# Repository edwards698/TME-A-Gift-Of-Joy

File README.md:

# Tech Master Event-The Gift Of Joy Christmas Project

The Gift of Joy is a festive project designed to bring the spirit of Christmas to life through a combination of 
electronics and creativity. This open-source project incorporates an Arduino Nano with an ATmega328 microcontroller, 
an LCD display (16x2), 5 LEDs, 5 100-ohm resistors, a 10K potentiometer, a push button, and a buzzer. Spreading the joy and celebrate the Christmas season by coming up with your own Gift of Joy open Source. 

Lets celebrate this festive season together 

### Tech Master Event

https://techmasterevent.com/

The Gift of Joy" is published as an open-source project, inviting others to learn from, modify, and contribute to the code and hardware design. By sharing the joy of Christmas through this project, the hope is to inspire others to build their own festive creations and share them with the community.

### Dependencies
```C++
#include <LiquidCrystal.h>
```

```C++
const int rs = 12, en = 11, d4 = 5, d5 = 4, d6 = 3, d7 = 2;
LiquidCrystal lcd(rs, en, d4, d5, d6, d7);
```

### Schematic 

## Components 
### Arduino Nano (ATmega328):
The brain of the project, responsible for controlling and coordinating all the connected components.

### LCD Display (16x2): 
This display serves as the interface, providing visual feedback and information about the project.

### 5 LEDs with 100-ohm resistors: 
These LEDs are used to create a colorful light display, representing the joy and festivity of Christmas.

### 10K Potentiometer: 
The potentiometer can be used to adjust settings or parameters, adding an element of user interaction to the project.

### Push Button:
A push button allows users to trigger specific actions or functions, enhancing the interactivity of the project.

### LED Display: 
The 5 LEDs can be programmed to light up in different patterns or sequences, creating visually appealing light displays.

### Interactive Features:
Program the push button to trigger the buzzer to play Christmas melodies.

### Adjustable Settings:
Utilize the potentiometer to allow users to adjust settings

### Buzzer Melodies: 
Program the buzzer to play festive tunes or sound effects, enhancing the overall Christmas experience.

"The Gift of Joy" is published as an open-source project, inviting others to learn from, modify, and contribute to the code and hardware design. By sharing the joy of Christmas through this project, the hope is to inspire others to build their own festive creations and share them with the community.

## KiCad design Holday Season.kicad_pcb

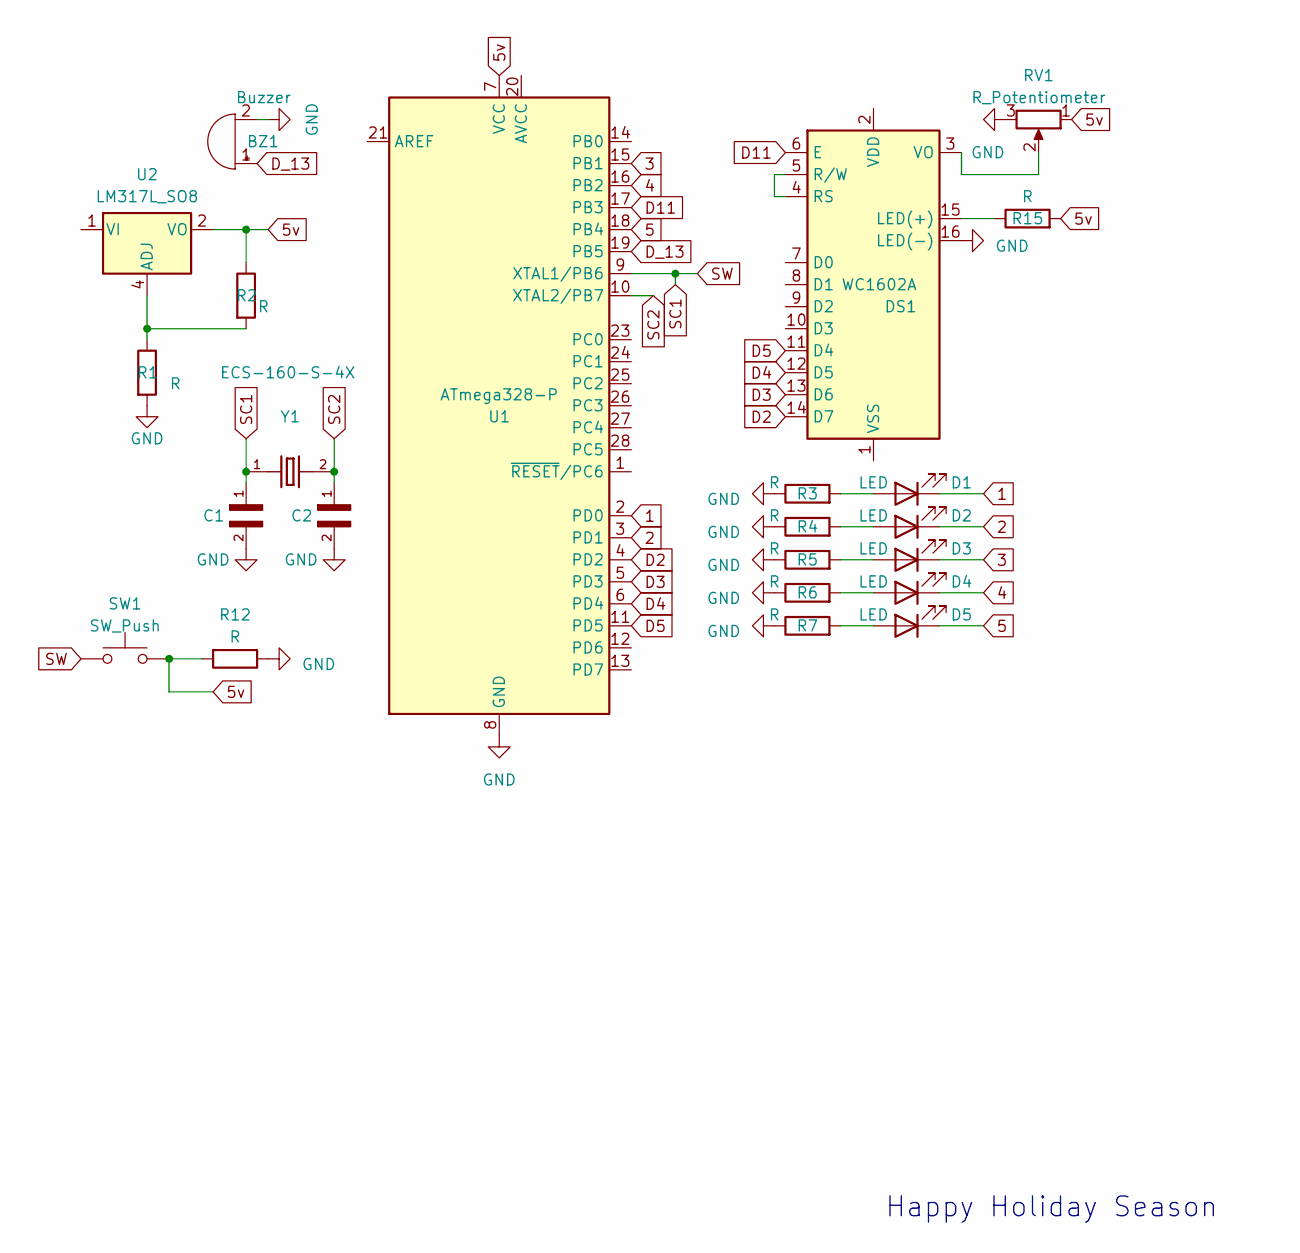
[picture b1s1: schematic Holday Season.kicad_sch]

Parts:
BZ1: Buzzer; XTAL_ECS-160-S-4X
C1, C2: DE11XRA220KN4AP01F; CAP_DE11XRA220KN4AP01F; PARTREV Jun. 2019
D1, D2, D3, D4, D5: LED; LED_D5.0mm_Clear
DS1: WC1602A
R1, R2, R3, R4, R5, R6, R7, R12, R15: R; R_Axial_DIN0309_L9.0mm_D3.2mm_P15.24mm_Horizontal
RV1: R_Potentiometer; Potentiometer_ACP_CA9-V10_Vertical
SW1: SW_Push; SW_PUSH_6mm
U1: ATmega328-P; DIP-28_W7.62mm
U2: LM317L_SO8; SOIC-8_3.9x4.9mm_P1.27mm
Y1: ECS-160-S-4X; XTAL_ECS-160-S-4X

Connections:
1: D1.1 (K), U1.2 (PD0)
2: D2.1 (K), U1.3 (PD1)
3: D3.1 (K), U1.15 (PB1)
4: D4.1 (K), U1.16 (PB2)
5: D5.1 (K), U1.18 (PB4)
5v: R2.1, R12.2, R15.2, RV1.1, SW1.2, U1.7 (VCC), U2.2 (VO), U2.3 (VO), U2.6 (VO), U2.7 (VO)
D2: DS1.14 (D7), U1.4 (PD2)
D3: DS1.13 (D6), U1.5 (PD3)
D4: DS1.12 (D5), U1.6 (PD4)
D5: DS1.11 (D4), U1.11 (PD5)
D11: DS1.6 (E), U1.17 (PB3)
D_13: BZ1.1 (-), U1.19 (PB5)
GND: BZ1.2 (+), C1.2, C2.2, DS1.16 (LED(-)), R1.2, R3.1, R4.1, R5.1, R6.1, R7.1, R12.1, RV1.3, U1.8 (GND), U1.22 (GND)
unnamed: D1.2 (A), R3.2
unnamed: D2.2 (A), R4.2
unnamed: D3.2 (A), R5.2
unnamed: D4.2 (A), R6.2
unnamed: D5.2 (A), R7.2
unnamed: DS1.15 (LED(+)), R15.1
unnamed: DS1.4 (RS), DS1.5 (R/W)
unnamed: DS1.3 (VO), RV1.2
unnamed: R1.1, R2.2, U2.4 (ADJ)
SC1: C1.1, SW1.1, U1.9 (XTAL1/PB6), Y1.1
SC2: C2.1, U1.10 (XTAL2/PB7), Y1.2

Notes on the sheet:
Happy Holiday Season

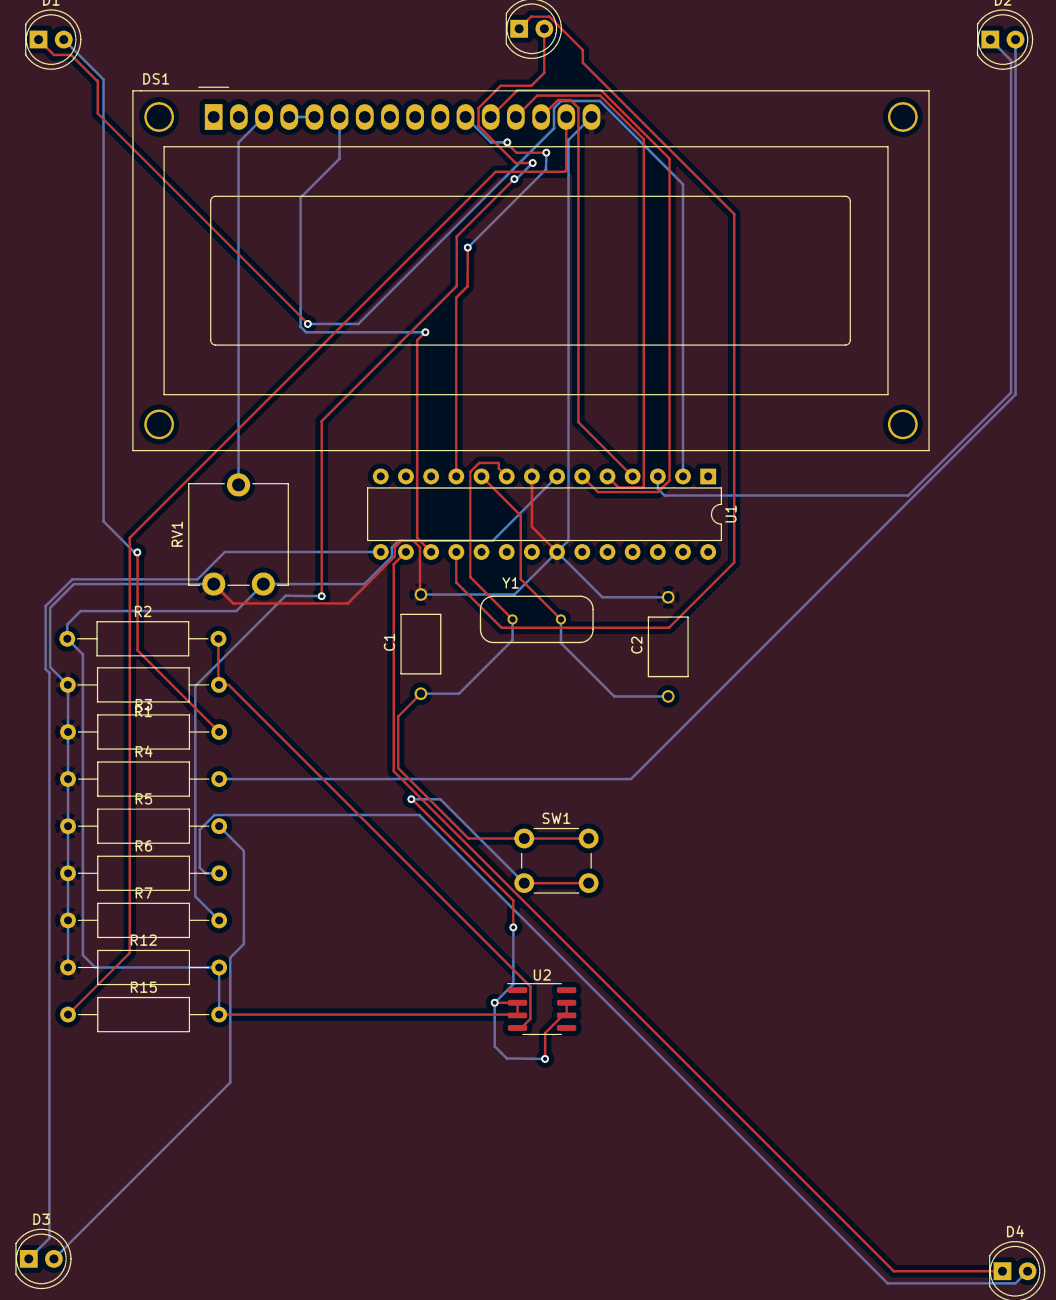
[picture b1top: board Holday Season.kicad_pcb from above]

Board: 2 copper layers, 22 parts (0 on the bottom side), 23 nets.

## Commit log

2023-11-06 Pilot
2023-11-06 Update on pilot
2023-11-13 The way to jingle bell
